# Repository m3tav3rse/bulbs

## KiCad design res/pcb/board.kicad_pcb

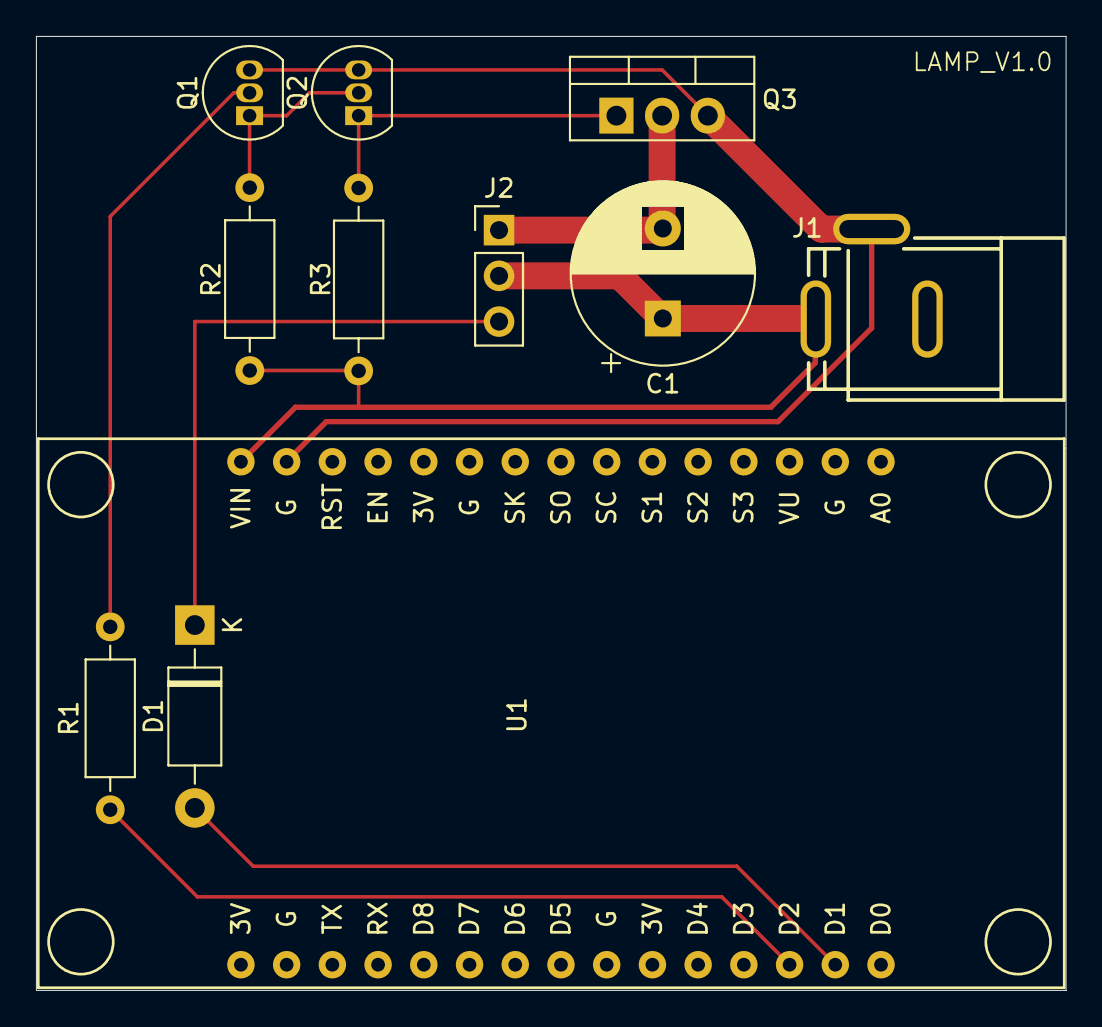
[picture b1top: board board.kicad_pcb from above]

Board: 2 copper layers, 57.2 x 53.0 mm, 11 parts (0 on the bottom side), 9 nets.

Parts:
C1: 1000µF; CP_Radial_D10.0mm_P5.00mm
D1: 1N4007; D_DO-41_SOD81_P10.16mm_Horizontal
J1: FC68148; CLIFF_FC68148(DC-10A)
J2: WS2812B (header); PinHeader_1x03_P2.54mm_Vertical
Q1, Q2: BC547; TO-92_Inline
Q3: IRF540N; TO-220-3_Vertical
R1, R2, R3: 10k; R_Axial_DIN0207_L6.3mm_D2.5mm_P10.16mm_Horizontal
U1: NodeMCU 3.0 (ESP-12E); NodeMCU-LoLinV3

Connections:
+5V: C1.1, J1.1, J2.2, R2.2, R3.2, U1.15 (VIN)
GND: J1.2, Q1.3 (E), Q2.3 (E), Q3.3 (S), U1.14 (GND)
unnamed: D1.2 (A), U1.29 (D1(GPIO5))
unnamed: D1.1 (K), J2.3
unnamed: C1.2, J2.1, Q3.2 (D)
unnamed: Q1.2 (B), R1.2
unnamed: Q1.1 (C), Q2.2 (B), R2.1
unnamed: Q2.1 (C), Q3.1 (G), R3.1
unnamed: R1.1, U1.28 (D2(GPIO4))

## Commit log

2023-09-03 Add project files
2023-09-30 Change directory structure
2023-09-30 Add main gitignore
2023-11-22 Add bulbs-cli
2024-03-17 Use absolute imports instead of appending to PATH
2024-05-27 Add additional asserts
2024-05-27 Fix syntax error
2024-05-27 mod/conf.py: handle JSONDecodeError
2024-05-30 Fix ruff errors/warnings
2024-05-30 Add NeoPixel stub for testing
2024-05-30 add mpy justfile recipes, not tested
2024-05-30 Add automatic device discovery
